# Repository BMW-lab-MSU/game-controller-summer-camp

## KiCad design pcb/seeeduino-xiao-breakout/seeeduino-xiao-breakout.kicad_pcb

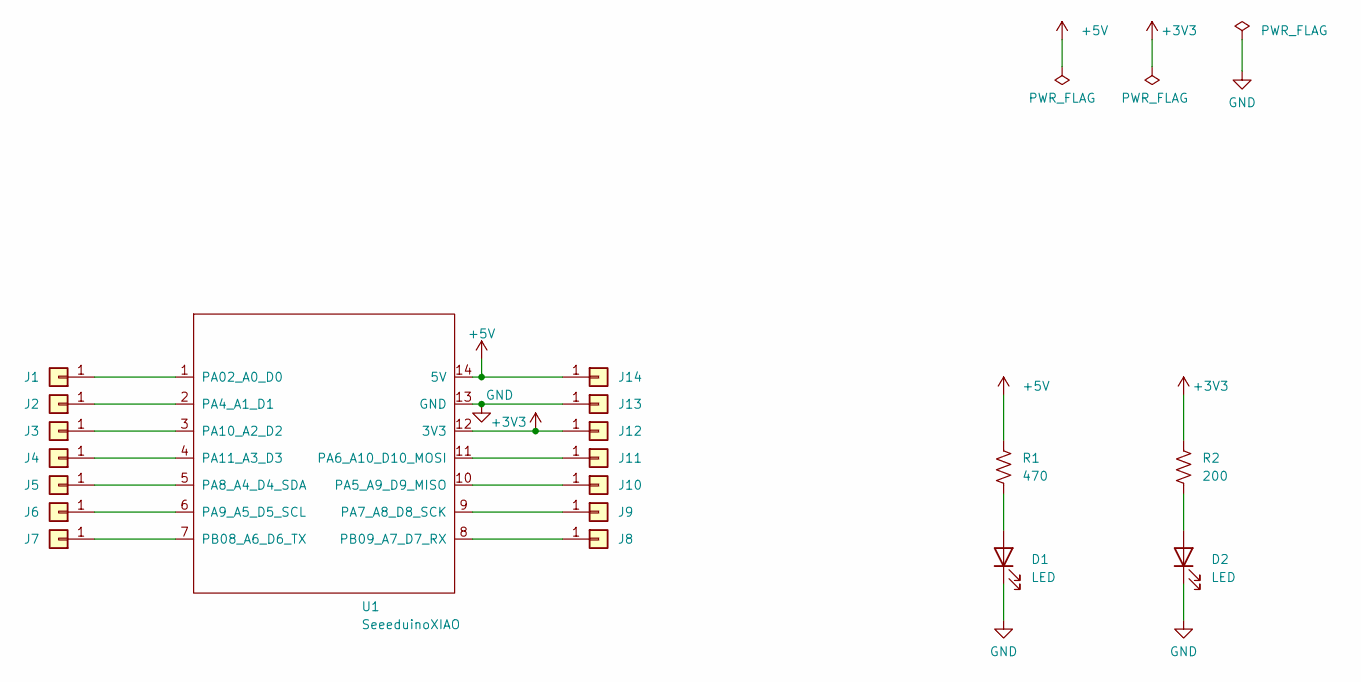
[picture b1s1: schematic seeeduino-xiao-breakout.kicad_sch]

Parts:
D1, D2: LED; LED_1206_3216Metric_Pad1.42x1.75mm_HandSolder
J1, J2, J3, J4, J5, J6, J7, J8, J9, J10, J11, J12, J13, J14: Conn_01x01_hole; con_01x01_edge
R1: 470; R_1206_3216Metric_Pad1.30x1.75mm_HandSolder
R2: 200; R_1206_3216Metric_Pad1.30x1.75mm_HandSolder
U1: SeeeduinoXIAO; Seeeduino XIAO-MOUDLE14P-2.54-21X17.8MM

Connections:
+3V3: J12.1, R2.1, U1.12 (3V3)
+5V: J14.1, R1.1, U1.14 (5V)
GND: D1.1 (K), D2.1 (K), J13.1, U1.13 (GND)
unnamed: D1.2 (A), R1.2
unnamed: D2.2 (A), R2.2
unnamed: J1.1, U1.1 (PA02_A0_D0)
unnamed: J2.1, U1.2 (PA4_A1_D1)
unnamed: J3.1, U1.3 (PA10_A2_D2)
unnamed: J4.1, U1.4 (PA11_A3_D3)
unnamed: J5.1, U1.5 (PA8_A4_D4_SDA)
unnamed: J6.1, U1.6 (PA9_A5_D5_SCL)
unnamed: J7.1, U1.7 (PB08_A6_D6_TX)
unnamed: J8.1, U1.8 (PB09_A7_D7_RX)
unnamed: J9.1, U1.9 (PA7_A8_D8_SCK)
unnamed: J10.1, U1.10 (PA5_A9_D9_MISO)
unnamed: J11.1, U1.11 (PA6_A10_D10_MOSI)

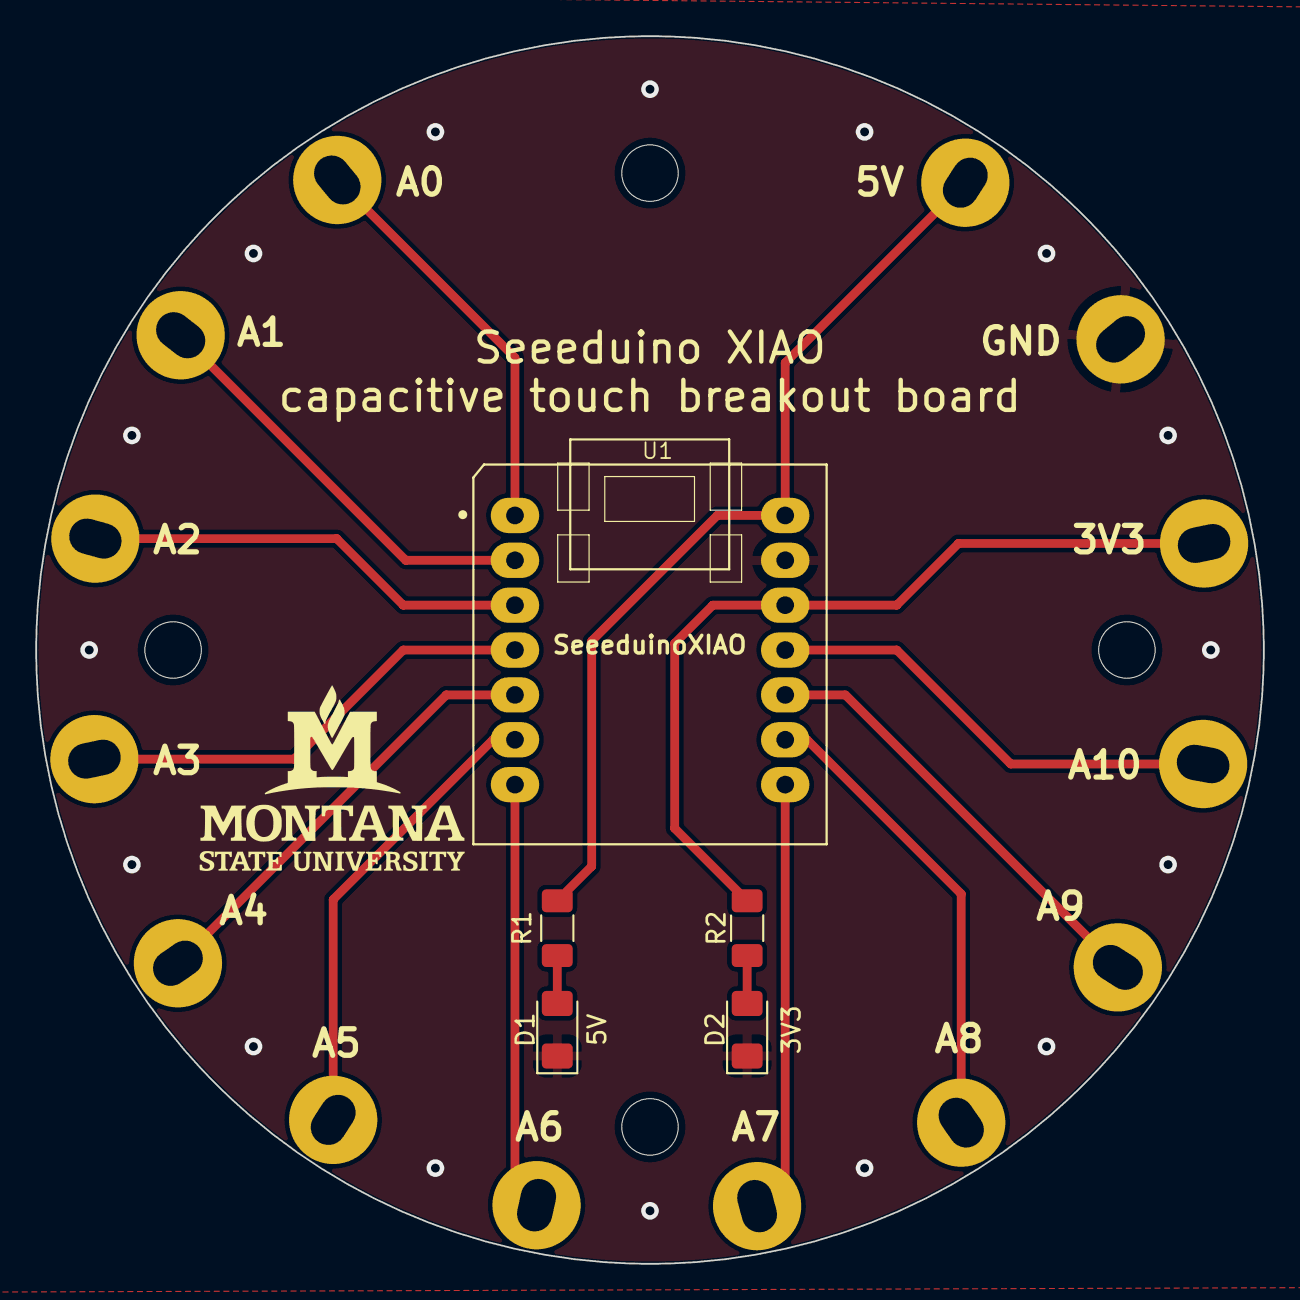
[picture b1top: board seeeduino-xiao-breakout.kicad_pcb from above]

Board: 2 copper layers, 69.5 x 69.5 mm, 20 parts (1 on the bottom side), 16 nets.

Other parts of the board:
QR*****: https://github.com/BMW-lab-MSU/game-controller-su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; github-repo-qrcode

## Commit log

2022-05-23 add seeeduino breakout pcb
2022-06-17 traffic light arduino code
2022-06-17 turn on and off an led with the touch sensor
2022-06-17 arduino code for the game controller
2024-04-05 move arduino sketches into subfolder
2024-04-05 add notes with links to parts
2024-05-14 increase power indicator resistor values
    The previous resistors made the LEDs far brighter than they needed to be
2024-05-14 make edge connector hole larger for alligator clips
    Previously, the hole was a little small for the alligator clips to
    actually latch onto. It wasn't a big deal, but hopefully the new
    slightly larger oval hole works better.
2024-05-14 update footprint type to through-hole instead of smd
2024-05-14 update seeduino footprint type and add spot for name on silkscreen
2024-05-14 add qr code and url
2024-05-14 generate new gerber files
2024-05-14 ignore macOS .DS_Store and some kicad files
2024-05-17 make qr code url show up on silkscreen
2024-05-21 create bom for pcb
2024-05-21 add bom for all parts
2024-06-11 add slides from previous year
2024-06-11 add minimal arudino setup instructions
2024-06-11 spell Seeed right
2024-06-17 revamp slides for first day
2024-06-17 move arudino sketches into subfolders
    The arduino IDE requires that the sketch is in a folder of the same
    name.
2024-06-17 add outline section slides for day 2
2024-06-17 add blank arduino files for demos and activities
2024-06-17 add comments to traffic light example
2024-06-17 add example for turning on led
2024-06-17 add example of naming an input/output pin with a variable
2024-06-18 update slides; add c syntax overview
2024-06-18 use camelCase to be consistent with Arduino functions
2024-06-18 add serial port hello world
2024-06-18 add serial input example
2024-06-18 add blinking led
2024-06-20 improve variable names
2024-06-20 add serial led switch
2024-06-20 add comment
2024-06-20 add rest of section outlines
